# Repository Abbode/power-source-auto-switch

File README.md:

# power-source-auto-switch
This module will provide power to your project via main and backup power sources.

You connect the two power sources to the module and it will do the following:

* When your main source is working properly it will  
  provide you circuit power from this source.
 * When your main source goes offline it will automatically  
  disconnect the main source and connect to backup source.
 * When your main source come back online it will automatically  
  disconnect the backup source and goes back to the main source.

The two source are completely isolated for safety reasons.
The module uses SMD pads, best way to use it is re-flow soldering.
The module supports up to 40V and 4.5A.

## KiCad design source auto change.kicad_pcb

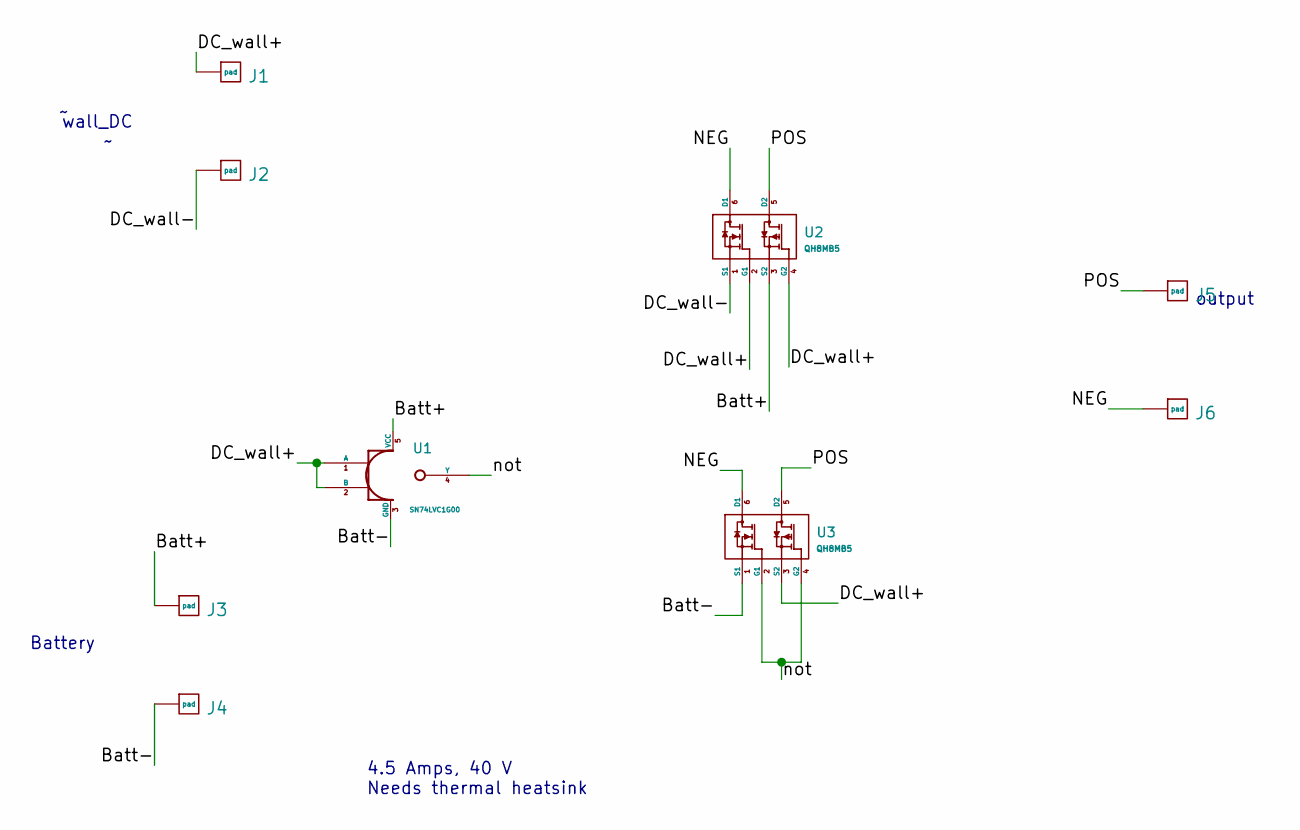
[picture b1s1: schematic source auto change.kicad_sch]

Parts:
J1, J2, J3, J4, J5, J6: pad; pad 2.2*1.35 mm
U1: SN74LVC1G00; SN74LVC1G00DRYR
U2, U3: QH8MB5; QH8MB5TCR

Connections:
/Batt+: J3.1 (pad), U1.5 (VCC), U2.3 (S2)
/Batt-: J4.1 (pad), U1.3 (GND), U3.1 (S1)
/DC_wall+: J1.1 (pad), U1.1 (A), U1.2 (B), U2.2 (G1), U2.4 (G2), U3.3 (S2)
/DC_wall-: J2.1 (pad), U2.1 (S1)
/NEG: J6.1 (pad), U2.6 (D1), U3.6 (D1)
/POS: J5.1 (pad), U2.5 (D2), U3.5 (D2)
/not: U1.4 (Y), U3.2 (G1), U3.4 (G2)

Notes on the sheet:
Battery
4.5 Amps, 40 V Needs thermal heatsink
output
wall_DC

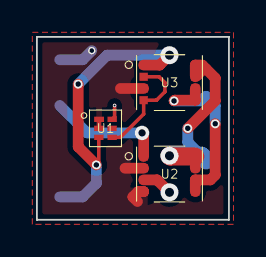
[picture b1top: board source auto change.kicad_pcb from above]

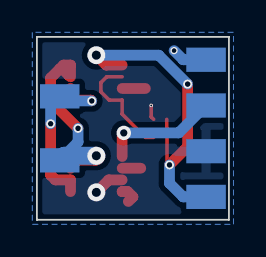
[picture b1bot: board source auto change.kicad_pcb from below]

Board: 2 copper layers, 10.7 x 10.2 mm, 9 parts (6 on the bottom side), 7 nets.

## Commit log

2022-10-10 adding description to README
2022-10-10 creating license
2022-10-10 adding project files
2022-10-10 Create qwe
2022-10-10 adding 3D files
2022-10-31 update the look of markdown readme file
